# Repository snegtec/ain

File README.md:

/*****************************************************************************
*
* AIN Led Module
* a simple led module with a microcontroller for Petzl Duo Led headlamp
* 
* Note: This is just a hobby project. I am not connected in any way with 
* Petzl company.
* 
* version: 0.1 (November 2020)
* author: Erik Kos
*          snegtec.com
*          snegtec@outlook.com
* 
* Copyright (C) 2014-2016 Erik Kos
* 
* License:
*   application, source code - GNU General Public License
*   hardware (schematics, pcb design) - Creative Commons Attribution 
*   Share-Alike license (CC BY-SA 4.0)
* 
****************************************************************************/

Used tools
* compiler: Atmel Studio 6
* application for pcb design: Eagle 6.5.0.

Notes/problems/bugs/limitations:
* This is very simple module. Don't expect exciting features.
* One 7135 driver is enough for one side FR4 pcb.
* There has to be a schottky diode. Standard diode disables change of modes when battery is out. If you want to use BAT54C SOT23 package (or similar) you have to change the pcb.
* It is enough to give 10uF ceramic capacitor. Memory is back up well - ATTiny takes below 1uA in power down state.
* ATtiny13 has too small flash memory to be good for such project. If you want to add some features - use ATMega328 or similar.
* The pcb size is an approximation. Check the size and alignment of power pins before ordering a pcb.
* Soldering pins for ISP may be tricky.

time to discharge (to 0,9v per accu, approximatelly): 
* main mode: 3h 
* 1/2 mode: 6h
* 1/4 mode: 12h
* dim mode: ?h

/****************************************************************************/

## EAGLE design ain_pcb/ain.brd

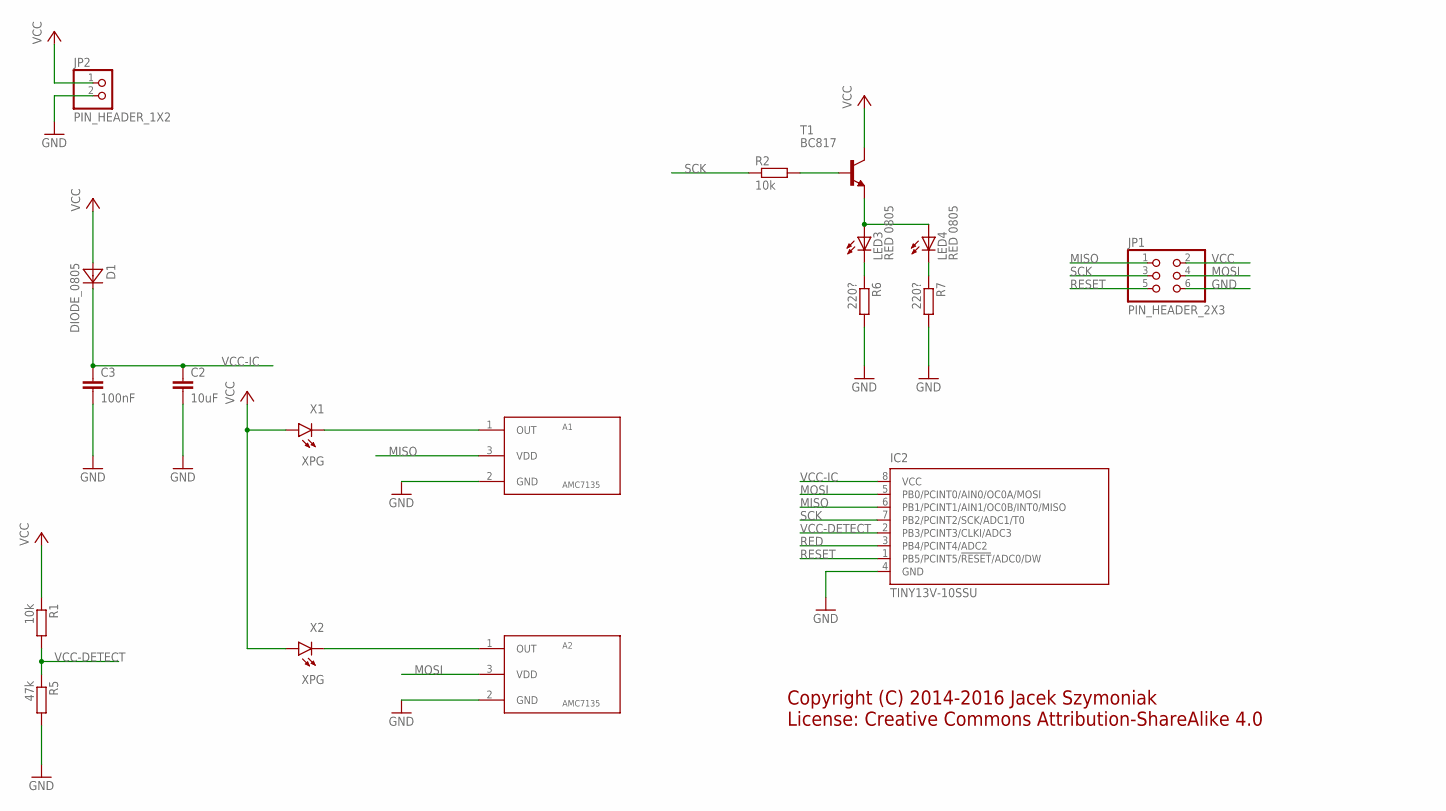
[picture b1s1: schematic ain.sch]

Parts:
A1, A2: AMC7135; SOT-89
C2: 10uF; C0805
C3: 100nF; C0805
D1: DIODE_0805; 0805
IC2: TINY13V-10SSU; 8S1
JP1: PIN_HEADER_2X3
JP2: PIN_HEADER_1X2
LED3, LED4: RED 0805; SML0805
R1, R2: 10k; M0805
R5: 47k; M0805
R6, R7: 220?; M0805
T1: BC817; SOT23-BEC
X1, X2: XPG

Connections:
GND: A1.2 (GND), A2.2 (GND), C2.2, C3.2, IC2.4 (GND), JP1.6, JP2.2, R5.2, R6.2, R7.2
MISO: A1.3 (VDD), IC2.6 (PB1/PCINT1/AIN1/OC0B/INT0/MISO), JP1.1
MOSI: A2.3 (VDD), IC2.5 (PB0/PCINT0/AIN0/OC0A/MOSI), JP1.4
unnamed: A2.1 (OUT), X2.2 (C)
unnamed: A1.1 (OUT), X1.2 (C)
unnamed: R2.2, T1.B
unnamed: LED3.A, LED4.A, T1.E
unnamed: LED4.C, R7.1
unnamed: LED3.C, R6.1
RED: IC2.3 (PB4/PCINT4/ADC2)
RESET: IC2.1 (PB5/PCINT5/!RESET!/ADC0/DW), JP1.5
SCK: IC2.7 (PB2/PCINT2/SCK/ADC1/T0), JP1.3, R2.1
VCC: D1.1 (A), JP1.2, JP2.1, R1.1, T1.C, X1.1 (A), X2.1 (A)
VCC-DETECT: IC2.2 (PB3/PCINT3/CLKI/ADC3), R1.2, R5.1
VCC-IC: C2.1, C3.1, D1.2 (C), IC2.8 (VCC)

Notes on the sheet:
Copyright (C) 2014-2016 Jacek Szymoniak License: Creative Commons Attribution-ShareAlike 4.0

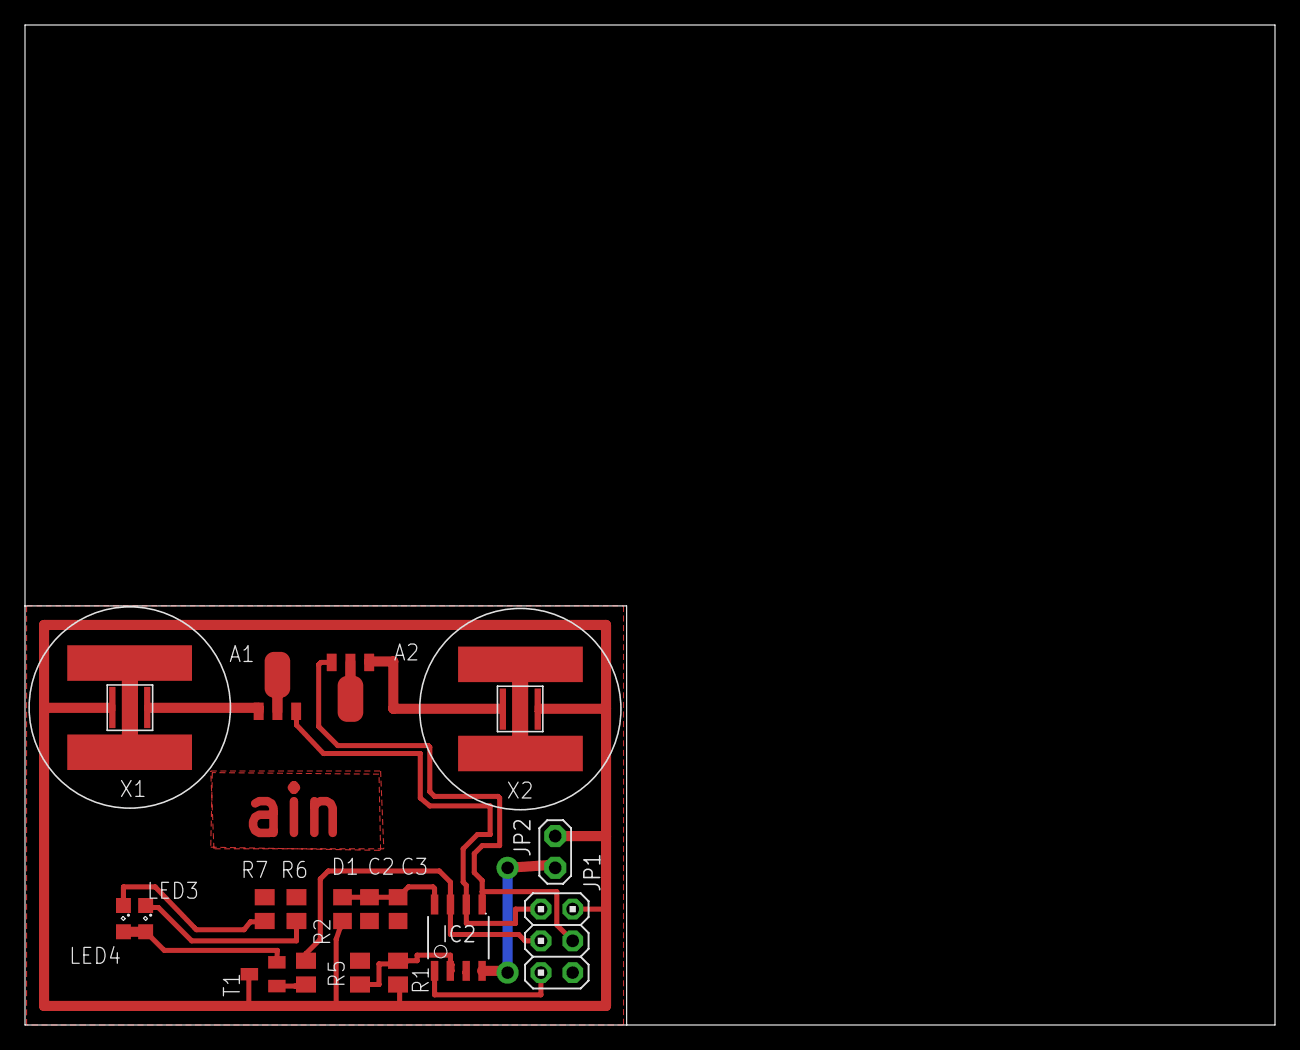
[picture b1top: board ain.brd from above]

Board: 2 copper layers, 100.0 x 80.0 mm, 18 parts (0 on the bottom side), 14 nets.

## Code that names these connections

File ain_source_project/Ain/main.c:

/*****************************************************************************
*
* AIN Led Module
* a simple led module with a microcontroller for Petzl Duo Led headlamp
* 
* Note: This is just a hobby project. I am not connected in any way with Petzl company.
* 
* version: 0.1 (March 2014)
* compiler: Atmel Studio 6
* author: Erik Kos
*          snegtec.com
*          snegtec@outlook.com
* 
* Copyright (C) 2014-2020 Erik Kos
* 
****************************************************************************
* 
* This program is free software; you can redistribute it and/or
* modify it under the terms of the GNU General Public License as
* published by the Free Software Foundation; either version 2 of the
* License, or (at your option) any later version.
*
* This program is distributed in the hope that it will be useful, but
* WITHOUT ANY WARRANTY; without even the implied warranty of
* MERCHANTABILITY or FITNESS FOR A PARTICULAR PURPOSE.  See the GNU
* General Public License for more details.
*
* You should have received a copy of the GNU General Public License
* along with this program; if not, write to the Free Software
* Foundation, Inc., 51 Franklin Street, Fifth Floor, Boston, MA  02110-1301, USA.
* 
****************************************************************************/

#include <avr/io.h>
#include <avr/interrupt.h>

// cpu frequency is defined in menu: Project/...properties/Toolchain/AVR/GNU C compiler/Symbols/F_CPU=128000UL
// cpu freqency is set by fuse bits not by definition by F_CPU; F_CPU is needed by delay.h

long timeCounter = 0;
short clicks = 0;
const short MAXTIME = 750;
long lastClickTime = 0;
long pcint3Time = 0;

short initialized = 0;
#define LEDA 1
#define LEDB 2
#define LEDRED 3

// attiny 13a
#define PIN_0 PB0
#define PIN_1 PB1
#define PIN_R PB2
#define PIN_VCC PB3

// change it in loadLastMode function
short mode = LEDA;

short brightness_a = 0;
short brightness_b = 0;
short brightness_r = 0;

short brightnesses[] = {255, 128, 64, 10};

void disablePin0()
{
	// disconnect pin OC0A
	// def TCCR0A &=~(1<<COM0A0);
	TCCR0A &=~(1<<COM0A1);
	
	// set low state
	PORTB &=~(1 << PIN_0);
}

void enablePin0()
{
	// connect pin OC0A
	// def TCCR0A &=~(1<<COM0A0);
	TCCR0A |=(1<<COM0A1);
}


void disablePin1()
{
	// disconnect pin OC0B
	// def TCCR0A &=~(1<<COM0B0);
	TCCR0A &=~(1<<COM0B1);

	// set low state
	PORTB &=~(1 << PIN_1);
}

void enablePin1()
{
	// connect pin OC0B
	// def TCCR0A &=~(1<<COM0B0);
	TCCR0A |= (1<<COM0B1);
}

void enableRed()
{
	// set pins as output
	DDRB = DDRB | (1 << PIN_R);
	
	// high state
	PORTB = PORTB | (1 << PIN_R);
}

void disableRed()
{
	// set pins as output
	// def DDRB = DDRB | (1 << PIN_R);
	
	// set low state
	PORTB &=~(1 << PIN_R);
}

void enablePwm()
{
	//************
	// pwm
	
	// pin configuration for pwm
	
	// DDR - set driver for OC0A and OC0B pins
	// set pins as output
	DDRB |= (1 << PIN_0);
	DDRB |= (1 << PIN_1);
	
	// waveform generation mode
	
	// mode 3, Fast PWM
	// def TCCR0B = TCCR0B & ~(1 << WGM02);
	TCCR0A = TCCR0A | (1 << WGM01);
	TCCR0A = TCCR0A |(1 << WGM00);
	
	
	// clock select
	// TCCR0B: CS02 CS01 CS00
	
	// clkio/1
	// def TCCR0B &=~ (1<<CS02);
	// def TCCR0B &=~ (1<<CS01);
	TCCR0B |= (1<<CS00);
}

void initialize_app()
{
	enablePwm();
	
	// enable interrupts for timer0
	TIMSK0 |= (1 << TOIE0);
	TIFR0 |= (1 << TOV0);
	
	
	//************
	// for checking presence of vcc
	
	// set pin as input
	DDRB = DDRB & ~(1 << PIN_VCC);
	
	// disable pullup
	PORTB &=~ (1<<PIN_VCC);

	// enable PCINT0 pin for interrupt
	PCMSK = PCMSK | (1<<PCINT3);
	
	// enable PCINT7..0 pins
	GIMSK = GIMSK | (1<<PCIE);
	
	//************
	// start interrupt system
	sei();
}


void disableTimer()
{
	// clkio/1
	// def TCCR0B &=~ (1<<CS02);
	// def TCCR0B &=~ (1<<CS01);
	TCCR0B &=~ (1<<CS00);
	
}

void enableTimer()
{
	// clkio/1
	// def TCCR0B &=~ (1<<CS02);
	// def TCCR0B &=~ (1<<CS01);
	TCCR0B |= (1<<CS00);
	
}

void loadBrightness()
{
	OCR0A = brightnesses[brightness_a];
	OCR0B = brightnesses[brightness_b];
}


void changeBrightness()
{
	if (mode == LEDA)
	{
		brightness_a++;
		if (brightness_a > 3)
		brightness_a = 0;
	}
	else if (mode == LEDB)
	{
		brightness_b++;
		if (brightness_b > 3)
		brightness_b = 0;
	}
	else if (mode == LEDRED)
	{
		brightness_r++;
		if (brightness_r > 3)
		brightness_r = 0;
	}
	loadBrightness();
}

void enableLed()
{
	if (mode == LEDA)
	{
		enablePin0();
		disablePin1();
		disableRed();
	}
	else if (mode == LEDB)
	{
		disablePin0();
		enablePin1();
		disableRed();
	}
	else if (mode == LEDRED)
	{
		disablePin0();
		disablePin1();
		enableRed();
	}
}


void changeMode()
{
	if (mode == LEDA)
	mode = LEDB;
	else if (mode == LEDB)
	{
		mode = LEDRED;
	}
	else if (mode == LEDRED)
	mode = LEDA;
	
	enableLed();
}

void disableLed()
{
	disablePin0();
	disablePin1();
	disableRed();
}

int main()
{
	initialize_app();
	
	brightness_a = 0;
	brightness_b = 0;
	brightness_r = 0;
	loadBrightness();
	
	mode = LEDA;
	enableLed();
	
	// main loop
	while (1)
	{}
	
}


ISR(TIM0_OVF_vect)
{
	
	// increment counters
	timeCounter++;
	
	// service of clicks
	if ((clicks == 1) && (timeCounter >= lastClickTime + (2 * MAXTIME)))
	{
		// wait one MAXTIME period to handle/service 1-clicks
		
		changeMode();
		
		lastClickTime = 0;
		
		timeCounter = 0;
		clicks = 0;
		} else if (clicks == 2) {
		// 2-click has to be taken immediately
		
		changeBrightness();
		
		lastClickTime = 0;
		
		timeCounter = 0;
		clicks = 0;
	}
	
	//************
	
	if (pcint3Time > 0 && timeCounter >= pcint3Time + 100)
	{
		pcint3Time = 0;
		
		// if vcc detection on PIN_VCC
		if (PINB & (1 << PIN_VCC))
		{
			lastClickTime = timeCounter;
			clicks++;
			
			enableLed();
		}
		else if ((PINB & (1 << PIN_VCC)) == 0)
		{
			// vcc is missing
			
			disableLed();
			
			disableTimer();
			
			// disable interrupts for timer0
			TIMSK0 &=~ (1 << TOIE0);
			TIFR0 &=~ (1 << TOV0);
			
			// start interrupt system
			sei();
			
			// enable idle state
			MCUCR |= (1 << SE);
			
			// power down
			MCUCR |= (1 << SM1);
			MCUCR &=~ (1 << SM0);
			
			// enter idle state
			asm ("sleep");
		}
	}
}


ISR(PCINT0_vect)
{
	pcint3Time = timeCounter;

	// if this interrupt disabled idle state
	if (MCUCR & (1 << SE))
	{
		// disable idle state
		MCUCR &=~ (1 << SE);
		
		enableTimer();
		
		// enable interrupts for timer0
		TIMSK0 |= (1 << TOIE0);
		TIFR0 |= (1 << TOV0);
		
	}
}

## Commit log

2016-05-11 full content
    full content - first public version
2020-11-14 Added some description and changed some information
